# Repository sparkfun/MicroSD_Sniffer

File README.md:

SparkFun microSD Sniffer
=========================

[*SparkFun microSD Sniffer (TOL-09419)*](https://www.sparkfun.com/products/9419)

Repository Contents
-------------------
* **/Hardware** - Eagle design files (.brd, .sch)
* **/Production** - Production panel files (.brd)

Documentation
--------------
* **[Hookup Guide](https://learn.sparkfun.com/tutorials/microsd-sniffer-hookup-guide)** - Basic hookup guide for the microSD Sniffer.

Product Versions
----------------
* [TOL-09419](https://www.sparkfun.com/products/9419)- Version 10

License Information
-------------------

This product is _**open source**_! 

Please review the LICENSE.md file for license information. 

If you have any questions or concerns on licensing, please contact techsupport@sparkfun.com.

Distributed as-is; no warranty is given.

- Your friends at SparkFun.

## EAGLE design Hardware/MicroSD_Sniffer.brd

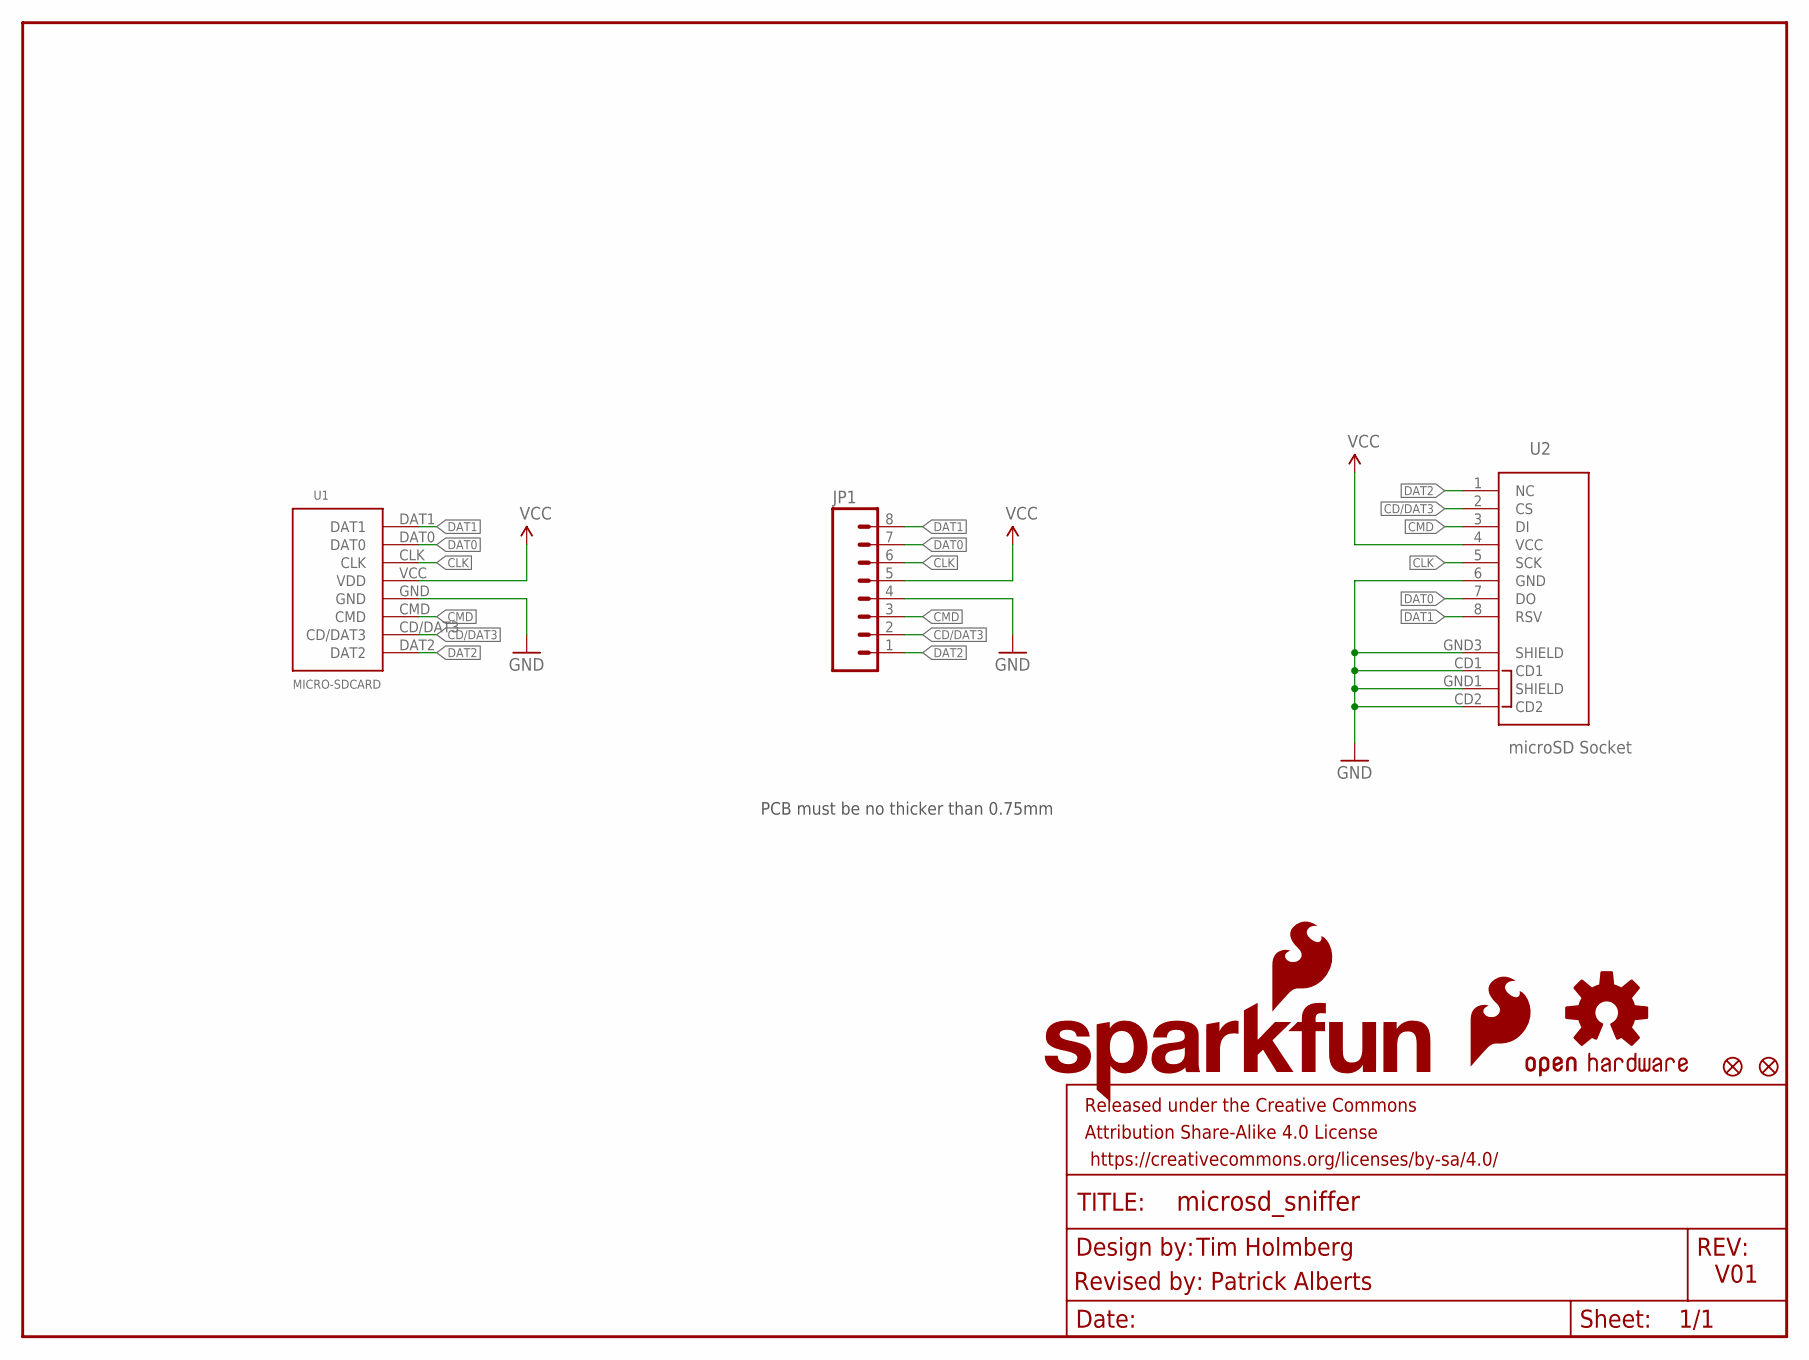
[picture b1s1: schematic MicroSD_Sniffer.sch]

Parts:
FID1, FID2: FIDUCIAL1X2; FIDUCIAL-1X2
FRAME1: FRAME-LETTER; CREATIVE_COMMONS
JP1: M08; 1X08
LOGO1: OSHW-LOGOM; OSHW-LOGO-M
LOGO2: SFE_LOGO_FLAME.2_INCH; SFE_LOGO_FLAME_.2
LOGO3: SFE_LOGO_NAME_FLAME.1_INCH; SFE_LOGO_NAME_FLAME_.1
U1: MICRO-SDCARD
U2: microSD Socket; MICROSD_1:1

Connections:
CD/DAT3: JP1.2, U1.CD/DAT3, U2.2 (CS)
CLK: JP1.6, U1.CLK, U2.5 (SCK)
CMD: JP1.3, U1.CMD, U2.3 (DI)
DAT0: JP1.7, U1.DAT0, U2.7 (DO)
DAT1: JP1.8, U1.DAT1, U2.8 (RSV)
DAT2: JP1.1, U1.DAT2, U2.1 (NC)
GND: JP1.4, U1.GND, U2.6 (GND), U2.CD1, U2.CD2, U2.GND1 (SHIELD), U2.GND3 (SHIELD)
VCC: JP1.5, U1.VCC (VDD), U2.4 (VCC)

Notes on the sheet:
PCB must be no thicker than 0.75mm
V01
Revised by: Patrick Alberts
Tim Holmberg

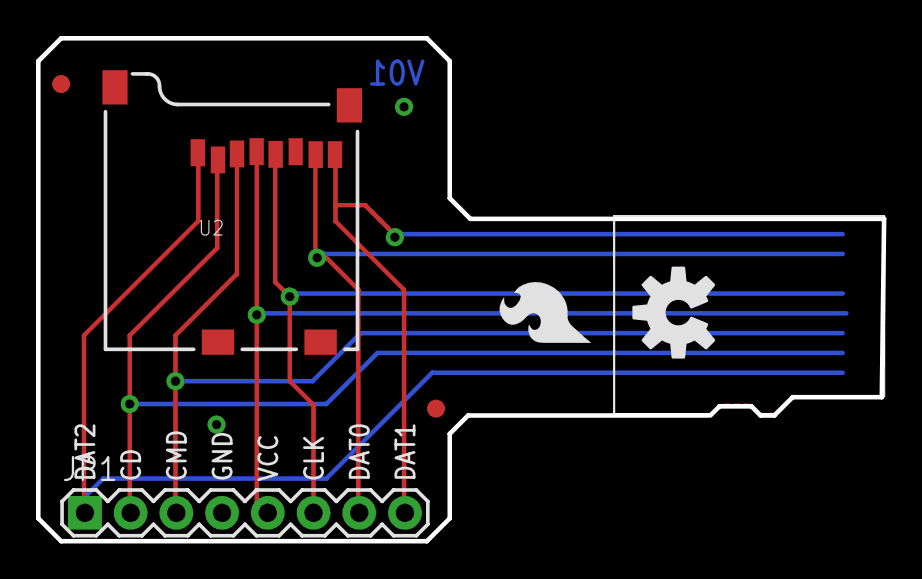
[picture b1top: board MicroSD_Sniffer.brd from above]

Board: 2 copper layers, 47.0 x 27.9 mm, 9 parts (1 on the bottom side), 8 nets.

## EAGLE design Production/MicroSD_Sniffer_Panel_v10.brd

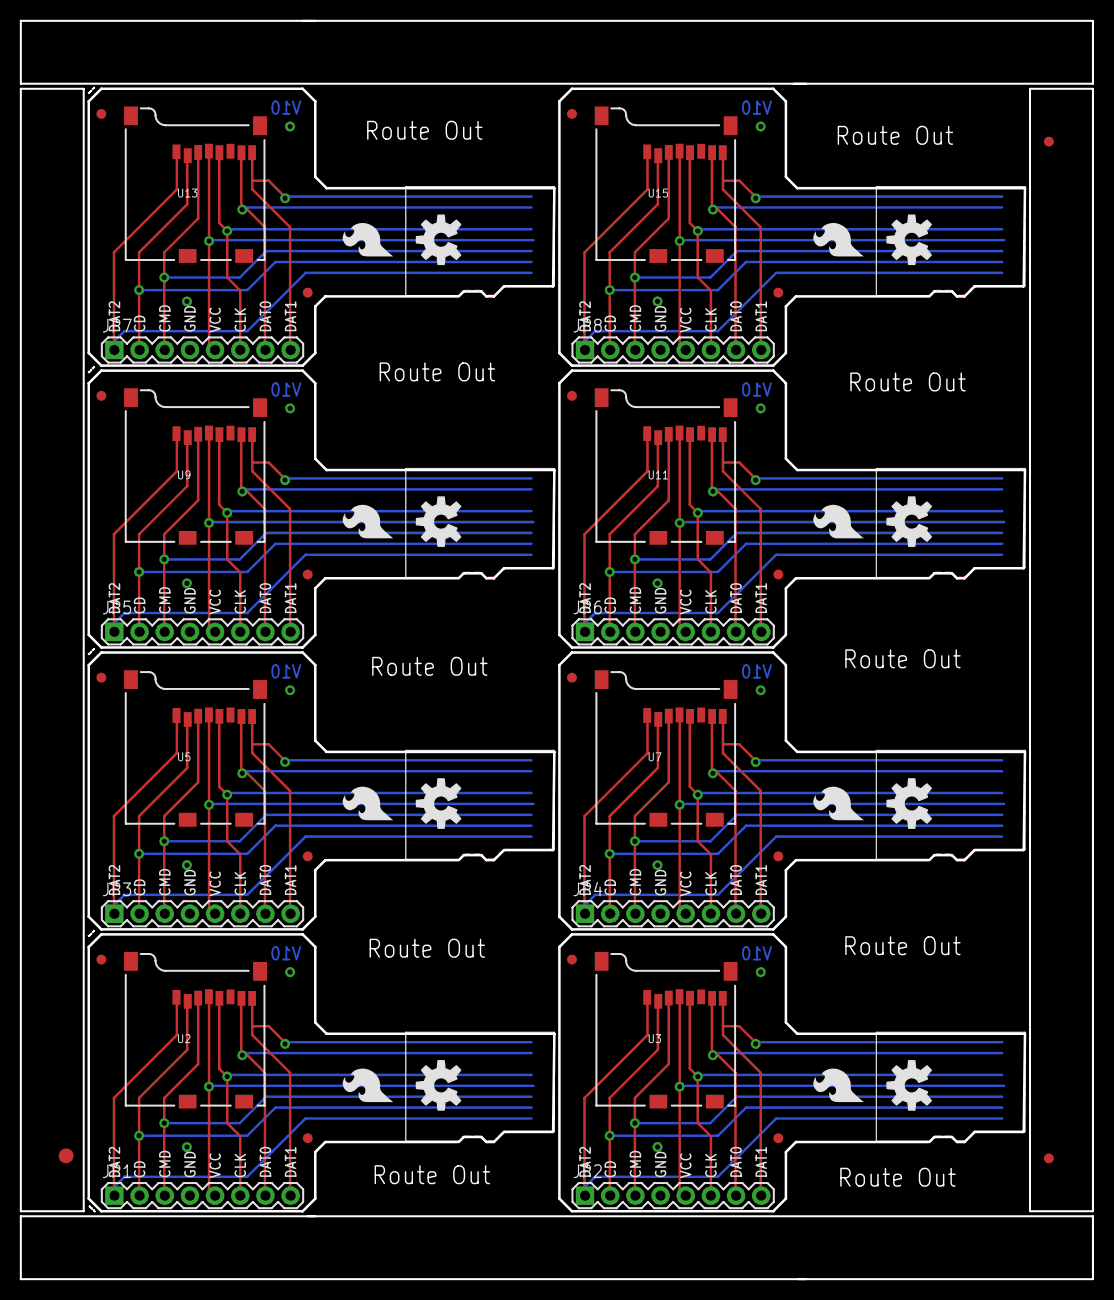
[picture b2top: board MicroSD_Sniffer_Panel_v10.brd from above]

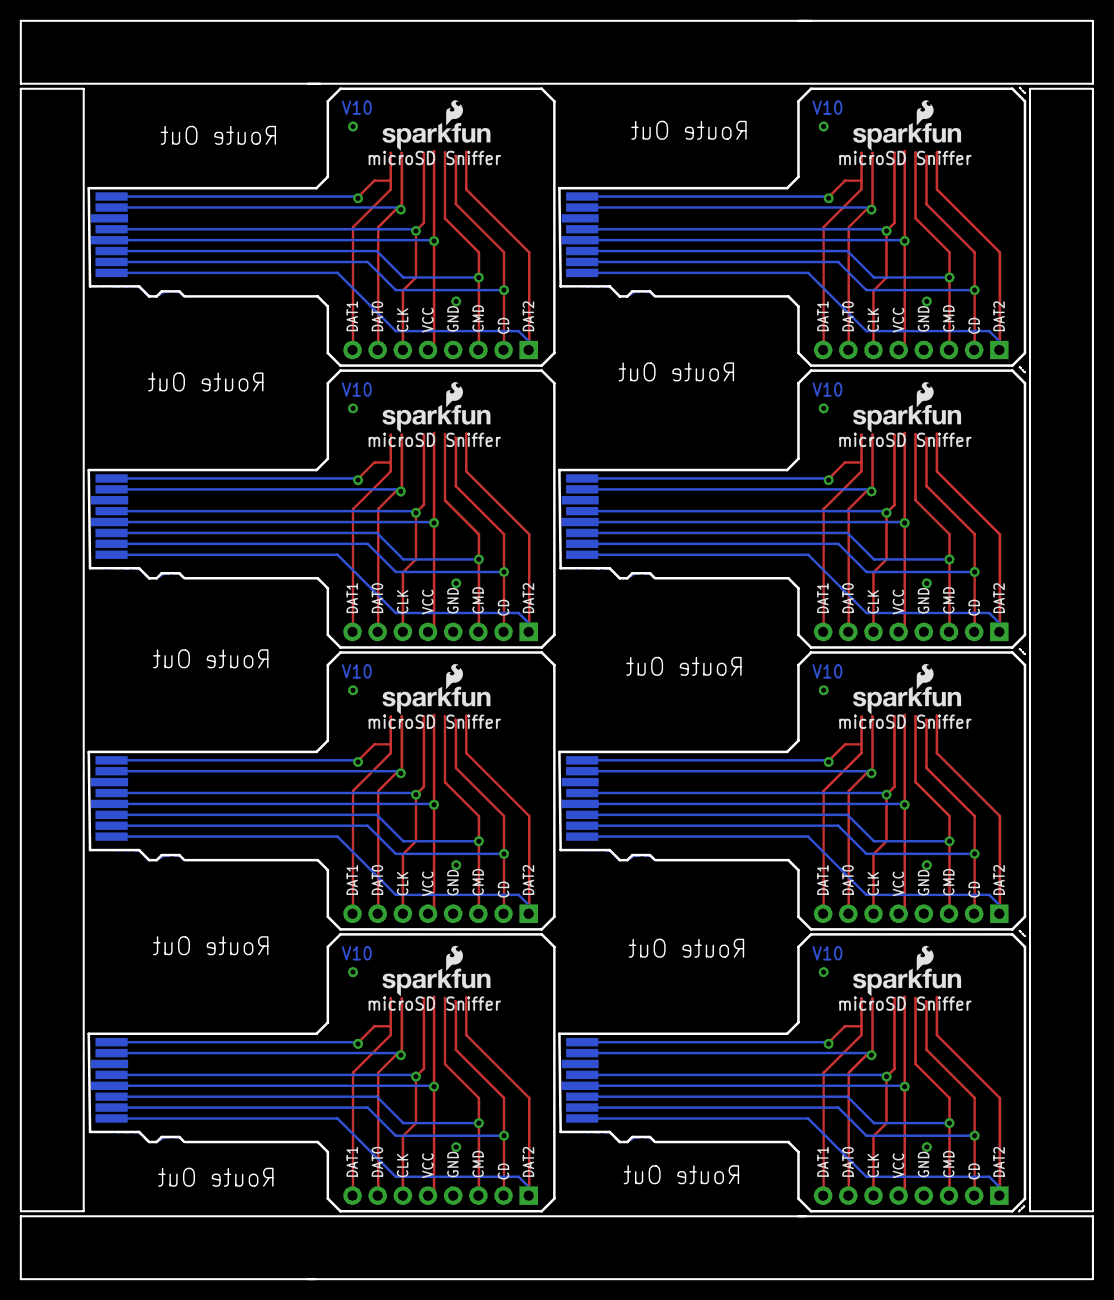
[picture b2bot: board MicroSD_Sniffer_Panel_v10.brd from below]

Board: 2 copper layers, 108.2 x 126.9 mm, 67 parts (8 on the bottom side), 64 nets.

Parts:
E$1: FIDUCIAL-1.5X3
E$4, E$8: FIDUCIAL-1X2
FID1, FID2, FID3, FID4, FID5, FID6, FID7, FID8, FID9, FID10, FID11, FID12, FID13, FID14, FID15, FID16: FIDUCIAL1X2; FIDUCIAL-1X2
JP1, JP2, JP3, JP4, JP5, JP6, JP7, JP8: 1X08
LOGO1, LOGO4, LOGO7, LOGO10, LOGO13, LOGO16, LOGO19, LOGO22: OSHW-LOGOM; OSHW-LOGO-M
LOGO2, LOGO5, LOGO8, LOGO11, LOGO14, LOGO17, LOGO20, LOGO23: SFE_LOGO_FLAME.2_INCH; SFE_LOGO_FLAME_.2
LOGO3, LOGO6, LOGO9, LOGO12, LOGO15, LOGO18, LOGO21, LOGO24: SFE_LOGO_NAME_FLAME.1_INCH; SFE_LOGO_NAME_FLAME_.1
U1, U4, U6, U8, U10, U12, U14, U16: MICRO-SDCARD
U2, U3, U5, U7, U9, U11, U13, U15: microSD Socket; MICROSD_1:1

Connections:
CD/DAT1: JP2.2, U3.2, U4.CD/DAT3
CD/DAT2: JP3.2, U5.2, U6.CD/DAT3
CD/DAT3: JP1.2, U1.CD/DAT3, U2.2
CD/DAT4: JP4.2, U7.2, U8.CD/DAT3
CD/DAT5: JP5.2, U9.2, U10.CD/DAT3
CD/DAT6: JP6.2, U11.2, U12.CD/DAT3
CD/DAT7: JP7.2, U13.2, U14.CD/DAT3
CD/DAT8: JP8.2, U15.2, U16.CD/DAT3
CLK: JP1.6, U1.CLK, U2.5
CLK1: JP2.6, U3.5, U4.CLK
CLK2: JP3.6, U5.5, U6.CLK
CLK3: JP4.6, U7.5, U8.CLK
CLK4: JP5.6, U9.5, U10.CLK
CLK5: JP6.6, U11.5, U12.CLK
CLK6: JP7.6, U13.5, U14.CLK
CLK7: JP8.6, U15.5, U16.CLK
CMD: JP1.3, U1.CMD, U2.3
CMD1: JP2.3, U3.3, U4.CMD
CMD2: JP3.3, U5.3, U6.CMD
CMD3: JP4.3, U7.3, U8.CMD
CMD4: JP5.3, U9.3, U10.CMD
CMD5: JP6.3, U11.3, U12.CMD
CMD6: JP7.3, U13.3, U14.CMD
CMD7: JP8.3, U15.3, U16.CMD
DAT0: JP1.7, U1.DAT0, U2.7
DAT1: JP1.8, U1.DAT1, U2.8
DAT2: JP1.1, U1.DAT2, U2.1
DAT3: JP2.8, U3.8, U4.DAT1
DAT4: JP2.7, U3.7, U4.DAT0
DAT5: JP2.1, U3.1, U4.DAT2
DAT6: JP3.8, U5.8, U6.DAT1
DAT7: JP3.7, U5.7, U6.DAT0
DAT8: JP3.1, U5.1, U6.DAT2
DAT9: JP4.8, U7.8, U8.DAT1
DAT10: JP4.7, U7.7, U8.DAT0
DAT11: JP4.1, U7.1, U8.DAT2
DAT12: JP5.8, U9.8, U10.DAT1
DAT13: JP5.7, U9.7, U10.DAT0
DAT14: JP5.1, U9.1, U10.DAT2
DAT15: JP6.8, U11.8, U12.DAT1
DAT16: JP6.7, U11.7, U12.DAT0
DAT17: JP6.1, U11.1, U12.DAT2
DAT18: JP7.8, U13.8, U14.DAT1
DAT19: JP7.7, U13.7, U14.DAT0
DAT20: JP7.1, U13.1, U14.DAT2
DAT21: JP8.8, U15.8, U16.DAT1
DAT22: JP8.7, U15.7, U16.DAT0
DAT23: JP8.1, U15.1, U16.DAT2
GND: JP1.4, U1.GND, U2.6, U2.CD1, U2.CD2, U2.GND1, U2.GND3
GND1: JP2.4, U3.6, U3.CD1, U3.CD2, U3.GND1, U3.GND3, U4.GND
GND2: JP3.4, U5.6, U5.CD1, U5.CD2, U5.GND1, U5.GND3, U6.GND
GND3: JP4.4, U7.6, U7.CD1, U7.CD2, U7.GND1, U7.GND3, U8.GND
GND4: JP5.4, U9.6, U9.CD1, U9.CD2, U9.GND1, U9.GND3, U10.GND
GND5: JP6.4, U11.6, U11.CD1, U11.CD2, U11.GND1, U11.GND3, U12.GND
GND6: JP7.4, U13.6, U13.CD1, U13.CD2, U13.GND1, U13.GND3, U14.GND
GND7: JP8.4, U15.6, U15.CD1, U15.CD2, U15.GND1, U15.GND3, U16.GND
VCC: JP1.5, U1.VCC, U2.4
VCC1: JP2.5, U3.4, U4.VCC
VCC2: JP3.5, U5.4, U6.VCC
VCC3: JP4.5, U7.4, U8.VCC
VCC4: JP5.5, U9.4, U10.VCC
VCC5: JP6.5, U11.4, U12.VCC
VCC6: JP7.5, U13.4, U14.VCC
VCC7: JP8.5, U15.4, U16.VCC

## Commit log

2015-01-15 Initial commit with brd/sch
2015-01-23 Prelim QC Checklist
2015-01-23 Official QC checklist items
2015-02-17 changed fids to regular
2015-02-17 created panel v01
2015-04-22 Changed Version #
2015-04-22 deleted old panel
2015-04-23 created new v10 panel with correct copper version
2015-07-21 Adding in license file, .git files, updating directory names, readme cleanup

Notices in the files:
parts and their libraries:
SparkFun-Aesthetics: Licensing: Creative Commons ShareAlike 4.0 International - https://creativecommons.org/licenses/by-sa/4.0
SparkFun-Aesthetics: Released under the Creative Commons Attribution Share-Alike 4.0 License
SparkFun-Aesthetics: https://creativecommons.org/licenses/by-sa/4.0
